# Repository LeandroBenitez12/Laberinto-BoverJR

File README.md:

# Robot en Desarrollo para la Resolución de Laberintos 🚧

## Descripción del Proyecto

Este repositorio contiene el código y los recursos utilizados para el desarrollo de un robot resolvente de laberintos, creado por Leandro Benitez, Ezequiel Sierra iniciado en 2022 acompañado de nuestro Profesor Ing. Bustos Mariano en el "Industrial de Temperley" ,como parte de un emocionante proyecto para la resolución autónoma de laberintos y la participacion competitiva a nivel nacional en la LNR Argentina. Durante el proceso de creación, hemos estado trabajando arduamente para implementar algoritmos de búsqueda, controladores PID, y trabajar con sensores Sharp y la programación en un microcontrolador ESP32 con el entorno Arduino. También hemos diseñado y creado nuestras propias librerías específicas para el robot, además de experimentar con la utilización de máquinas de estados y Programación orientada a Objetos para lograr un funcionamiento eficiente y preciso.
Actualmente nos encontramos Sponsoreados por PCBWAY.COM donde diseñamos la nueva Version de Bover JR y esperamos competir durante 2023 y 2024 en la LNR , quiero agradecer a **PCBWAY** por financiar el PCB!!!

## Características del Proyecto en Desarrollo

- **Resolución autónoma de laberintos:** Estamos trabajando para permitir que el robot navegue y encuentre la salida de un laberinto sin intervención externa y en el menor tiempo posible.
- **Algoritmos de búsqueda:** Hemos comenzado a implementar diferentes algoritmos de búsqueda para dotar al robot de la capacidad de tomar decisiones inteligentes mientras explora el laberinto.
- **Controladores PID:** Utilizamos controladores PID para mejorar la precisión y estabilidad del robot al seguir una trayectoria y evitar desviaciones indeseadas.
- **Sensores Sharp:** Integración de sensores Sharp para detectar obstáculos y evitar colisiones durante el recorrido del laberinto.
- **ESP32 y Arduino:** El robot se basa en un ESP32 programado con el entorno Arduino, lo que nos brindó flexibilidad y recursos para desarrollar un sistema eficiente y la utilización de Bluetooth para debugear.
- **Librerías personalizadas:** Creamos librerías específicas para nuestro robot, lo que facilitó el manejo y organización del código.

## Estructura del Repositorio

- **/Software:** Aquí se encuentran los códigos que estuvimos trabajando en el laberinto con sus librerías.
- **/Design 3D:** Aqui se encuentran los 3D diseñados para el robot Bover JR 

## Cómo Contribuir

¡Valoramos cualquier contribución que puedas brindar para mejorar nuestro proyecto! Si deseas colaborar, sugerir mejoras o corregir problemas, sigue estos pasos:

1. Haz un fork de este repositorio y clona tu copia localmente.
2. Realiza los cambios y mejoras en tu rama, incluso si es para sugerir posibles soluciones o nuevas ideas.
3. Asegúrate de agregar o actualizar la documentación con tus contribuciones.
4. Realiza un pull request a nuestra rama principal para que podamos revisar y considerar tus aportes.

## Contacto

Nos encantaría recibir tus comentarios, sugerencias y cualquier tipo de feedback que nos ayude a mejorar nuestro proyecto. Si deseas ponerte en contacto con nosotros, no dudes en escribirnos a:

- Leandro Benitez: leandrobenitezz2004@gmail.com
- Empresa : bovergroup@gmail.com

## Sigue actualizado al proyecto siguiendonos en: 
<p align="left">

</p>

## Agradecimientos

Queremos expresar nuestro agradecimiento a todas las personas que nos han brindado apoyo y colaboración en este proyecto, especialmente a **PCBWAY.COM** por sponsorear este proyecto. ¡Sin su ayuda, no habríamos llegado tan lejos en nuestro desarrollo!

## Videos

https://github.com/LeandroBenitez12/Laberinto-BoverJR/assets/108737751/4792c012-6e11-466b-b290-4252d44b76c1

https://github.com/LeandroBenitez12/Laberinto-BoverJR/assets/108737751/9e88a07d-3f39-4b07-be96-34b641f0b9c9

https://github.com/LeandroBenitez12/Laberinto-BoverJR/assets/108737751/d4477cc3-5138-43af-baba-faa490c5ad7a

Estamos entusiasmados con los avances que hemos logrado hasta el momento, pero reconocemos que aún hay mucho trabajo por delante. Apreciamos tu comprensión y paciencia mientras continuamos mejorando y refinando nuestro robot resolvente de laberintos. Puedes seguir actualizado al proyecto siguiendonos en nuestras redes sociales:
🤖🏆

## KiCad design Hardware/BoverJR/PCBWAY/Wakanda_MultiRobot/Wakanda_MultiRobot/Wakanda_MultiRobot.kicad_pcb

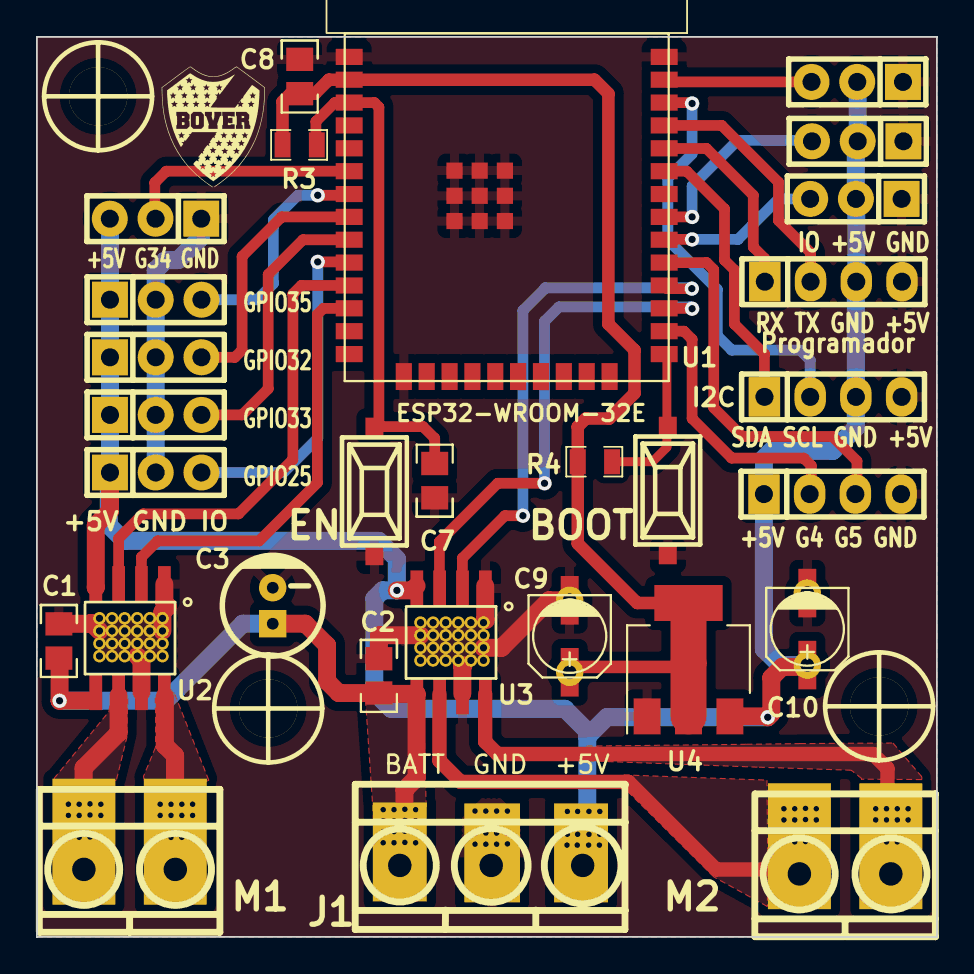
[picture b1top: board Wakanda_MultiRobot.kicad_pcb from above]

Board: 2 copper layers, 50.0 x 50.0 mm, 33 parts (0 on the bottom side), 28 nets.

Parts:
BOOT1: BOOT; Pulsador_SMD_2_BAJO
C1, C2, C7, C8: 100nF; C_0805
C3: 100uF 35V; CAP_ELEC_5x11mm
C9: 100uF; CAP_ELEC_SMD_4X5.5
C10: 10uF; CAP_ELEC_SMD_4X5.5
EN1: EN; Pulsador_SMD_2_BAJO
J1: Alimentacion; BORNERA3_AZUL_VIAS
J2, J4, J5, J6: Conn_01X03; Pin_Strip_3
J3: Sensor Distancia 1; Pin_Strip_3
J7: TATAMI Frontal Izquierdo; Pin_Strip_3
J8: Pin_Strip_3
J9: Programador; pin_strip_4
J10: I2C; pin_strip_4
J11: M1; BORNERA2_AZUL_VIAS
J12: M2; BORNERA2_AZUL_VIAS
J14: RANDOM; pin_strip_4
LOGO1: Mounting_Hole; Bover_Huella_frontal_FCU
P2, P3, P4: Mounting_Hole; Separador_M3_5mm
R3, R4: 10K; R_0805
SW1: START; Pin_Strip_3
U1: ESP32-WROOM-32E
U2, U3: TB67H451AFNG; SSOP-8_disipa
U4: AMS1117-3.3; SOT-223-3_TabPin2

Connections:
+3V3: C8.1, C9.1, R3.2, R4.2, U1.3V3, U4.2 (VO)
+5V: C10.1, J1.3, J2.1, J3.1, J4.1, J5.2, J6.2, J7.2, J8.1, J9.3, J10.3, J14.1, SW1.3, U2.4 (VREF), U3.4 (VREF), U4.3 (VI)
/EN: C7.1, EN1.2, R3.1, U1.9 (EN)
/GPIO4: J14.2, U1.24 (IO4)
/GPIO5: J14.3, U1.34 (IO5)
/IO0: BOOT1.2, R4.1, U1.23 (IO0)
/M_DER_A: U1.27 (IO17), U3.2 (IN2)
/M_DER_B: U1.25 (IO16), U3.3 (IN1)
/M_IZQ_A: U1.16 (IO27), U2.2 (IN2)
/M_IZQ_B: U1.15 (IO26), U2.3 (IN1)
/RXD: J9.1, U1.40 (RXD0)
/SCL: J10.2, U1.39 (IO22)
/SDA: J10.1, U1.42 (IO21)
/SENSOR1: J3.3, U1.13 (IO33)
/SENSOR2: J2.3, U1.14 (IO25)
/SENSOR3: J5.3, U1.38 (IO19)
/SENSOR4: J6.3, U1.35 (IO18)
/SENSOR5: J4.3, U1.11 (IO35)
/SENSOR6: J7.3, U1.36 (IO23)
/SENSOR7: J8.3, U1.12 (IO32)
/START: SW1.2, U1.10 (IO34)
/TXD: J9.2, U1.41 (TXD0)
GND: BOOT1.1, C1.2, C2.2, C3.2, C7.2, C8.2, C9.2, C10.2, EN1.1, J1.2, J2.2, J3.2, J4.2, J5.1, J6.1, J7.1, J8.2, J9.4, J10.4, J14.4, SW1.1, U1.GND, U2.1 (GND), U2.7 (RS), U3.1 (GND), U3.7 (RS), U4.1 (GND)
unnamed: J11.1, U2.6 (OUT1)
unnamed: J11.2, U2.8 (OUT2)
unnamed: J12.1, U3.6 (OUT1)
unnamed: J12.2, U3.8 (OUT2)
Vin: C1.1, C2.1, C3.1, J1.1, U2.5 (VM), U3.5 (VM)

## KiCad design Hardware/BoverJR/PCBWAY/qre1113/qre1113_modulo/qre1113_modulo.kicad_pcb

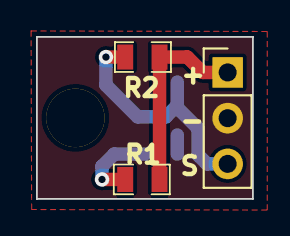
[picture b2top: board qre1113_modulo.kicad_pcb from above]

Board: 2 copper layers, 12.0 x 9.0 mm, 5 parts (1 on the bottom side), 4 nets.

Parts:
H1: HOLE; Separador_M3_5mm
J1: qre1113_out; PinHeader_1x03_P2.54mm_Vertical
R1: 100; R_0805
R2: 4k7; R_0805
U1: QRE1113GR; OnSemi_CASE100CY

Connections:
+3V3: J1.1, R1.1, R2.2
/OUT: J1.3, R2.1, U1.3
GND: J1.2, U1.2 (K), U1.4
unnamed: R1.2, U1.1 (A)

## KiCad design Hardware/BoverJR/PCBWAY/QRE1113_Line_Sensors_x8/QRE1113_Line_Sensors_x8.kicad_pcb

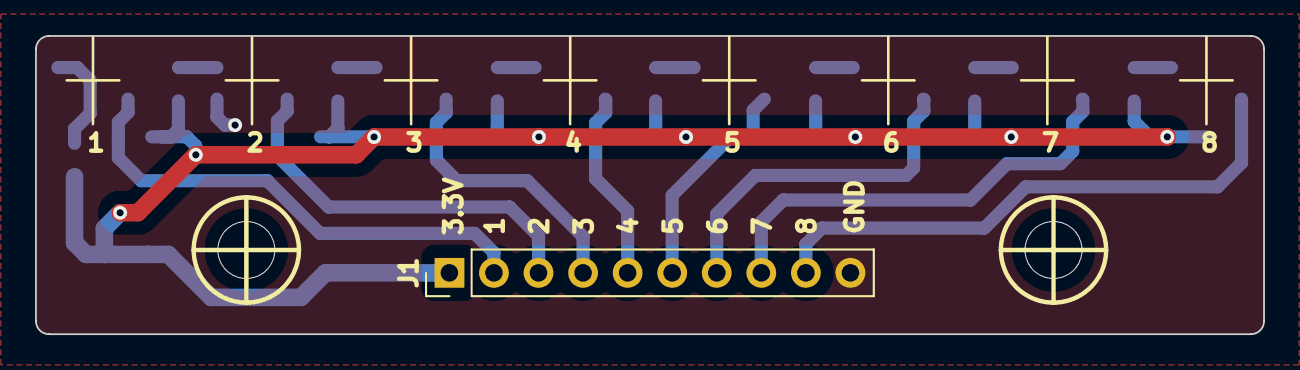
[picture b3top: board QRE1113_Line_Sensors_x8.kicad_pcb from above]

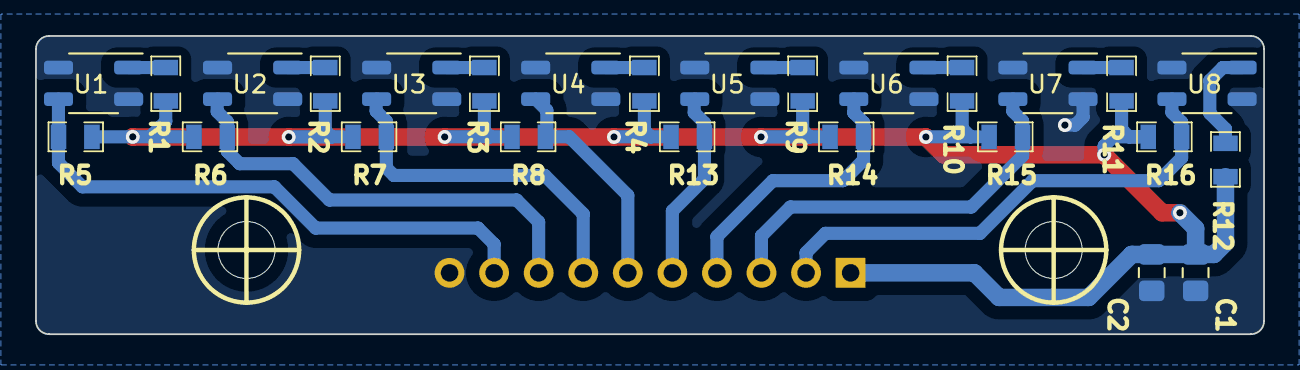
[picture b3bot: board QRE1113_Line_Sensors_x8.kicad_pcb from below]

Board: 2 copper layers, 70.0 x 17.0 mm, 29 parts (26 on the bottom side), 18 nets.

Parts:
C1, C2: 100nf; C_0805_2012Metric_Pad1.18x1.45mm_HandSolder
H1, H2: HOLE; Separador_M3_5mm
J1: Conn_01x10_Pin; PinHeader_1x10_P2.54mm_Vertical
R1, R2, R3, R4, R9, R10, R11, R12: 100; R_0805
R5, R6, R7, R8, R13, R14, R15, R16: 10k; R_0805
U1, U2, U3, U4, U5, U6, U7, U8: QRE1113GR; OnSemi_CASE100CY

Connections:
+3V3: C1.1, C2.1, J1.1, R1.1, R2.1, R3.1, R4.1, R5.2, R6.2, R7.2, R8.2, R9.1, R10.1, R11.1, R12.1, R13.2, R14.2, R15.2, R16.2
/OUT_1: J1.9, R5.1, U1.3
/OUT_2: J1.8, R6.1, U2.3
/OUT_3: J1.7, R7.1, U3.3
/OUT_4: J1.6, R8.1, U4.3
/OUT_5: J1.5, R13.1, U5.3
/OUT_6: J1.4, R14.1, U6.3
/OUT_7: J1.3, R15.1, U7.3
/OUT_8: J1.2, R16.1, U8.3
GND: C1.2, C2.2, J1.10, U1.2 (K), U1.4, U2.2 (K), U2.4, U3.2 (K), U3.4, U4.2 (K), U4.4, U5.2 (K), U5.4, U6.2 (K), U6.4, U7.2 (K), U7.4, U8.2 (K), U8.4
unnamed: R1.2, U1.1 (A)
unnamed: R2.2, U2.1 (A)
unnamed: R3.2, U3.1 (A)
unnamed: R4.2, U4.1 (A)
unnamed: R9.2, U5.1 (A)
unnamed: R10.2, U6.1 (A)
unnamed: R11.2, U7.1 (A)
unnamed: R12.2, U8.1 (A)

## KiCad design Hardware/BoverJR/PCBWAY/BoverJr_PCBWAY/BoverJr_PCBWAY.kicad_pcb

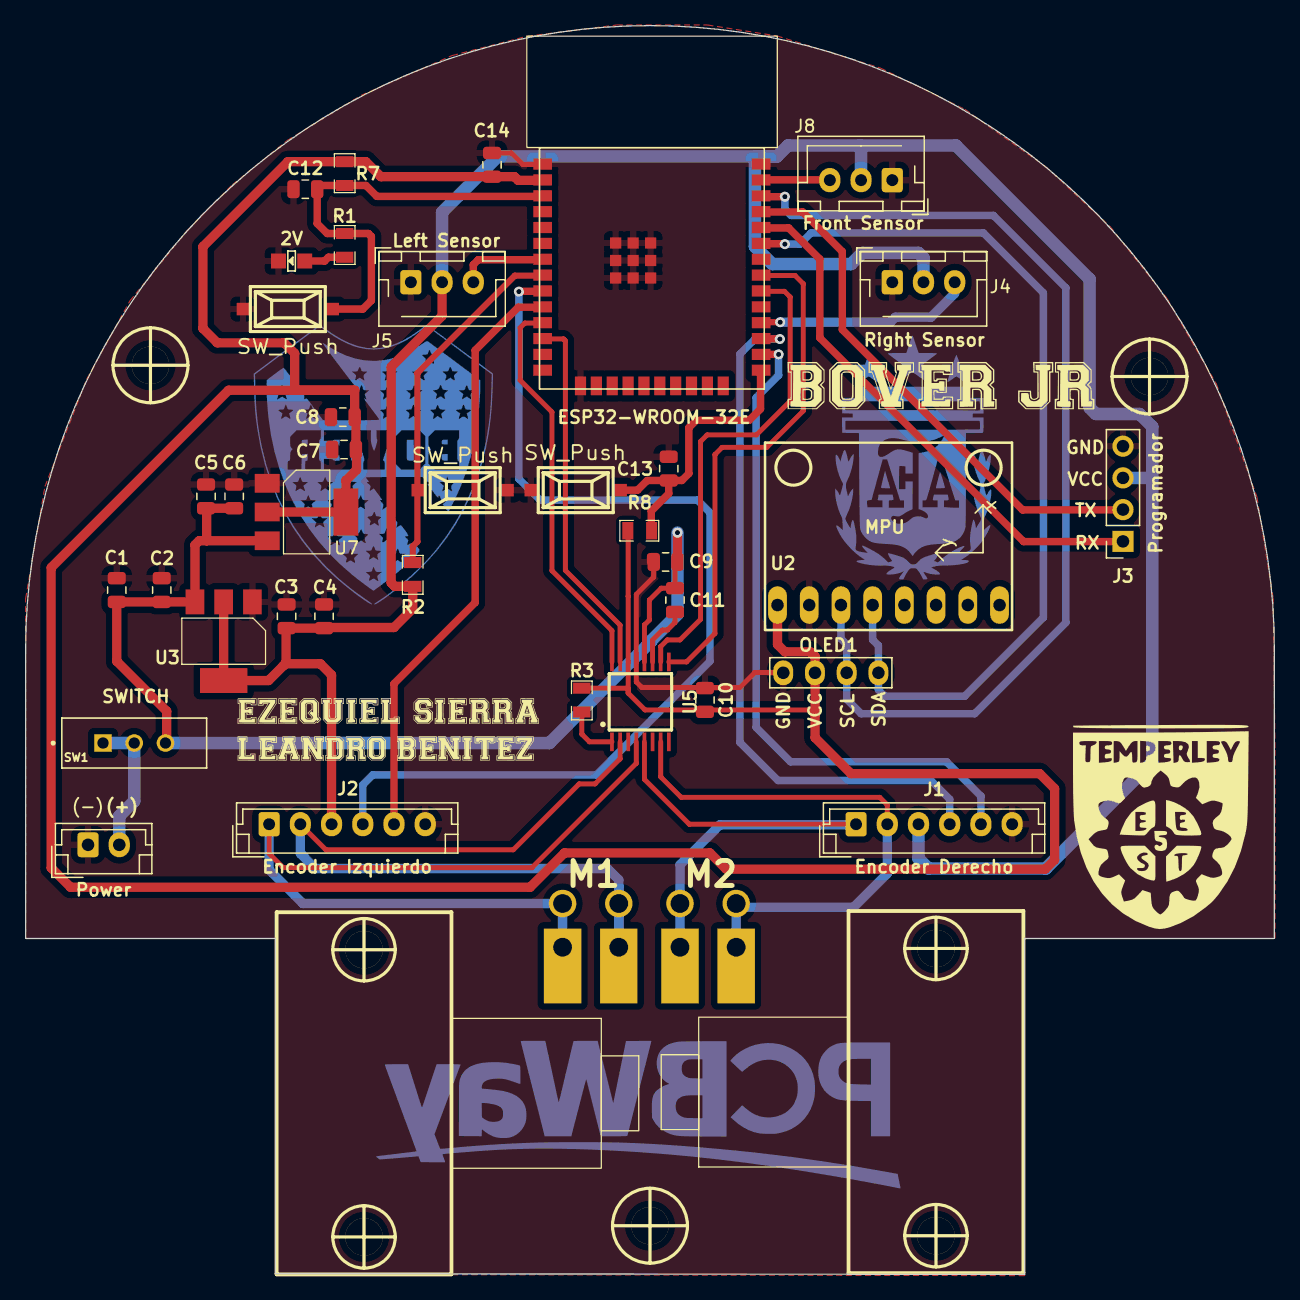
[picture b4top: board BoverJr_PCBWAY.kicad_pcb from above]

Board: 2 copper layers, 100.0 x 100.0 mm, 53 parts (1 on the bottom side), 30 nets.

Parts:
C1, C4, C5, C8, C9: 10uF; C_0805_2012Metric
C2, C3, C6, C7, C14: 100nF; C_0805_2012Metric
C10: 2,2uF; C_0805_2012Metric
C11: 10nF; C_0805_2012Metric
C12, C13: 1nf; C_0805_2012Metric
G1: LOGO_EESTN5_2; EESTN5
G2: LOGO; Bover_Huella_BCU_SOLK
G3: LOGO; AFA_BCU_filks
G6: LOGO; BOVER_NAME
G10: LOGO; Leandro
G11: LOGO; ezequiel
G14: LOGO; logo_pcbway
H1: Soporte_Motor_IZQ; Pololu_Micro_Con_Soporte_Simple
H2: Soporte_Motor_DER; Pololu_Micro_Con_Soporte_Simple
H3, H4, H5: Mounting_Hole; hole_3mm
J1: Encoder Derecho; JST_EH_B6B-EH-A_1x06_P2.50mm_Vertical
J2: Encoder Izquierdo; JST_EH_B6B-EH-A_1x06_P2.50mm_Vertical
J3: Programador; PinSocket_1x04_P2.54mm_Vertical
J4: Distancia_Der; JST_XH_B3B-XH-AM_1x03_P2.50mm_Vertical
J5: Distancia_Izq; JST_XH_B3B-XH-AM_1x03_P2.50mm_Vertical
J6, J7, J9, J11: Cable_PAD; Cable_Doble_1,5mm
J8: Distancia_Frontal; JST_XH_B3B-XH-AM_1x03_P2.50mm_Vertical
J10: 7.4v; JST_EH_B2B-EH-A_1x02_P2.50mm_Vertical
LED_ESP32: 2V; Led_0805
OLED1: SSD1306-SSD1306-128x64_OLED; 128x64OLED
R1: 470; R_0805
R2, R7: 10K; R_0805
R3: 47K; R_0805
R8: 1OK; R_0805
SW1: SW_SPDT; SW_MINI-SPDT-SW
SW_BOOT1: SW_Push; Pulsador_SMD_2_BAJO
SW_EN1: SW_Push; Pulsador_SMD_2_BAJO
SW_START1: SW_Push; Pulsador_SMD_2_BAJO
U1: ESP32-WROOM-32E
U2: MPU; MPU-6050
U3: AMS1117-5.0; SOT-223-3_TabPin2
U5: DRV8833; HTSSOP-16
U7: AMS1117-3.3; SOT-223-3_TabPin2

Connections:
+3.3V: C7.1, C8.1, C10.2, C14.1, OLED1.2 (VCC), R3.1, R7.2, R8.2, U1.3V3, U2.1 (VCC), U5.14 (VINT), U7.2 (VO)
+5V: C3.2, C4.1, J1.3, J2.3, J3.3, J4.2, J5.2, J8.2, R2.2, U3.2 (VO)
+BATT: J10.2, SW1.1 (A), SW1.2 (B)
/BOOT: C13.2, R8.1, SW_BOOT1.2, U1.23 (IO0)
/EN: C12.2, R1.2, R7.1, SW_EN1.2, U1.9 (EN)
/IR_DER: J5.3, U1.11 (IO35)
/IR_FRONTAL: J8.3, U1.36 (IO23)
/IR_IZQ: J4.3, U1.27 (IO17)
/M1_IN1: U1.38 (IO19), U5.9 (BIN1)
/M1_IN2: U1.35 (IO18), U5.10 (BIN2)
/M2_IN1: U1.15 (IO26), U5.16 (AIN1)
/M2_IN2: U1.16 (IO27), U5.15 (AIN2)
/OUT_A_MOTOR1: J1.1, J6.1, U5.5 (BOUT2)
/OUT_A_MOTOR2: J2.1, J9.1, U5.4 (AOUT2)
/OUT_B_MOTOR1: J1.2, J7.1, U5.7 (BOUT1)
/OUT_B_MOTOR2: J2.2, J11.1, U5.2 (AOUT1)
/OUT_M1_DA: J1.4, U1.25 (IO16)
/OUT_M1_DB: J1.5, U1.24 (IO4)
/OUT_M2_DA: J2.4, U1.13 (IO33)
/OUT_M2_DB: J2.5, U1.14 (IO25)
/RX: J3.1, U1.40 (RXD0)
/SCL: OLED1.3 (SCL), U1.39 (IO22), U2.3 (SCL)
/SDA: OLED1.4 (SDA), U1.42 (IO21), U2.4 (SDA)
/START: R2.1, SW_START1.2, U1.12 (IO32)
/TX: J3.2, U1.41 (TXD0)
GND: C1.2, C2.2, C3.1, C4.2, C5.2, C6.2, C7.2, C8.2, C9.1, C10.1, C12.1, C13.1, C14.2, J1.6, J2.6, J3.4, J4.1, J5.1, J8.1, J10.1, LED_ESP32.2 (K), OLED1.1 (GND), SW_BOOT1.1, SW_EN1.1, SW_START1.1, U1.GND, U2.2 (GND), U3.1 (GND), U5.13 (GND), U7.1 (GND)
unnamed: LED_ESP32.1 (A), R1.1
unnamed: C11.2, U5.11 (VCP)
unnamed: R3.2, U5.1 (nSLEEP)
VCC: C1.1, C2.1, C5.1, C6.1, C9.2, C11.1, SW1.3 (C), U3.3 (VI), U5.12 (VM), U7.3 (VI)

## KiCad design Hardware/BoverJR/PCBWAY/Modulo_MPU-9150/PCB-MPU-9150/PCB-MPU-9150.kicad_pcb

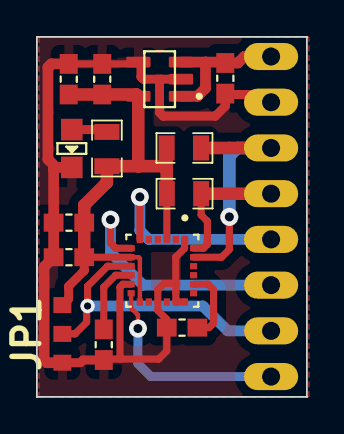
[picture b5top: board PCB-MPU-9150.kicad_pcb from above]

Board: 2 copper layers, 15.0 x 20.0 mm, 15 parts (1 on the bottom side), 12 nets.

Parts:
C1: 2.2nF; C_0603
C2, C3, C5: 100nF; C_0603
C4: 10nF; C_0603
C6: 10uF; C_0603
C7: 4.7uF; C_0603
JP1: Jump; R_0805
LED1: LED; Led_0805
P1: CONN_01X08; GY-521-MPU-6050
R1, R2: 10K; R_0805
R3: 1K; R_0805
U1: MPU-9150; MPU-9150-Qfn-24
U2: AP2112K-3.3; AP2112K-3.3-Sot25

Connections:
+3.3V: C3.1, C4.1, C5.2, C6.2, JP1.3 (B), R1.1, R2.1, R3.1, U1.3 (VDD), U1.8 (VLOGIC), U1.13 (VDD), U2.5 (VOUT)
/AD0: JP1.2 (C), P1.7, U1.9 (AD0)
/INT: P1.8, U1.12 (INT)
/SCL: P1.3, R2.2, U1.23 (SCL)
/SDA: P1.4, R1.2, U1.24 (SDA)
/XCL: P1.6, U1.7 (ES_CL)
/XDA: P1.5, U1.6 (ES_DA)
GND: C1.1, C2.1, C3.2, C4.2, C5.1, C6.1, C7.2, JP1.1 (A), LED1.2 (K), P1.2, U1.1 (CLKIN), U1.11 (FSYNC), U1.15 (GND), U1.17 (GND), U1.18 (GND), U2.2 (GND)
unnamed: LED1.1 (A), R3.2
unnamed: C1.2, U1.20 (CPOUT)
unnamed: C2.2, U1.10 (REGOUT)
VCC: C7.1, P1.1, U2.1 (VIN), U2.3 (EN)

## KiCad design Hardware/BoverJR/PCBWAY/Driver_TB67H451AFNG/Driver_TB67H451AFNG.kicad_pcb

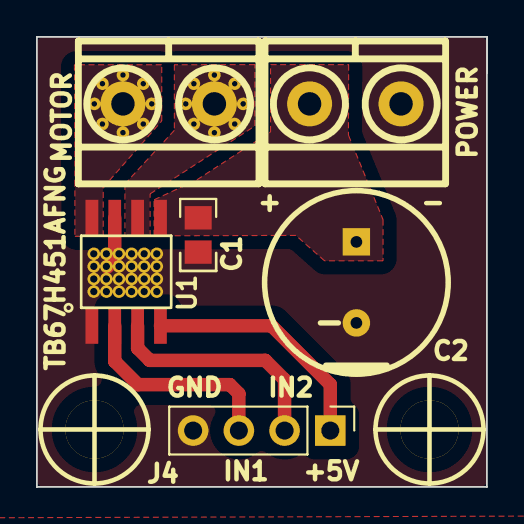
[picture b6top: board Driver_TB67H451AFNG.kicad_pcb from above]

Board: 2 copper layers, 25.0 x 25.0 mm, 8 parts (0 on the bottom side), 7 nets.

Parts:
C1: 100nF; C_0805
C2: 100uF 35V; CAP_ELEC_10X8mm
H1, H2: Mounting_Hole; Separador_M3_5mm
J1: POWER; BORNERA2_AZUL
J3: MOTOR; BORNERA2_AZUL_HOLES+
J4: Conn_01x04_Pin; PinHeader_1x04_P2.54mm_Vertical
U1: TB67H451AFNG; SSOP-8_disipa

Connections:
+5V: J4.1, U1.4 (VREF)
/M1A: J4.3, U1.2 (IN2)
/M1B: J4.2, U1.3 (IN1)
/Vin: C1.1, C2.1, J1.2, U1.5 (VM)
GND: C1.2, C2.2, J1.1, J4.4, U1.1 (GND), U1.7 (RS)
unnamed: J3.1, U1.6 (OUT1)
unnamed: J3.2, U1.8 (OUT2)

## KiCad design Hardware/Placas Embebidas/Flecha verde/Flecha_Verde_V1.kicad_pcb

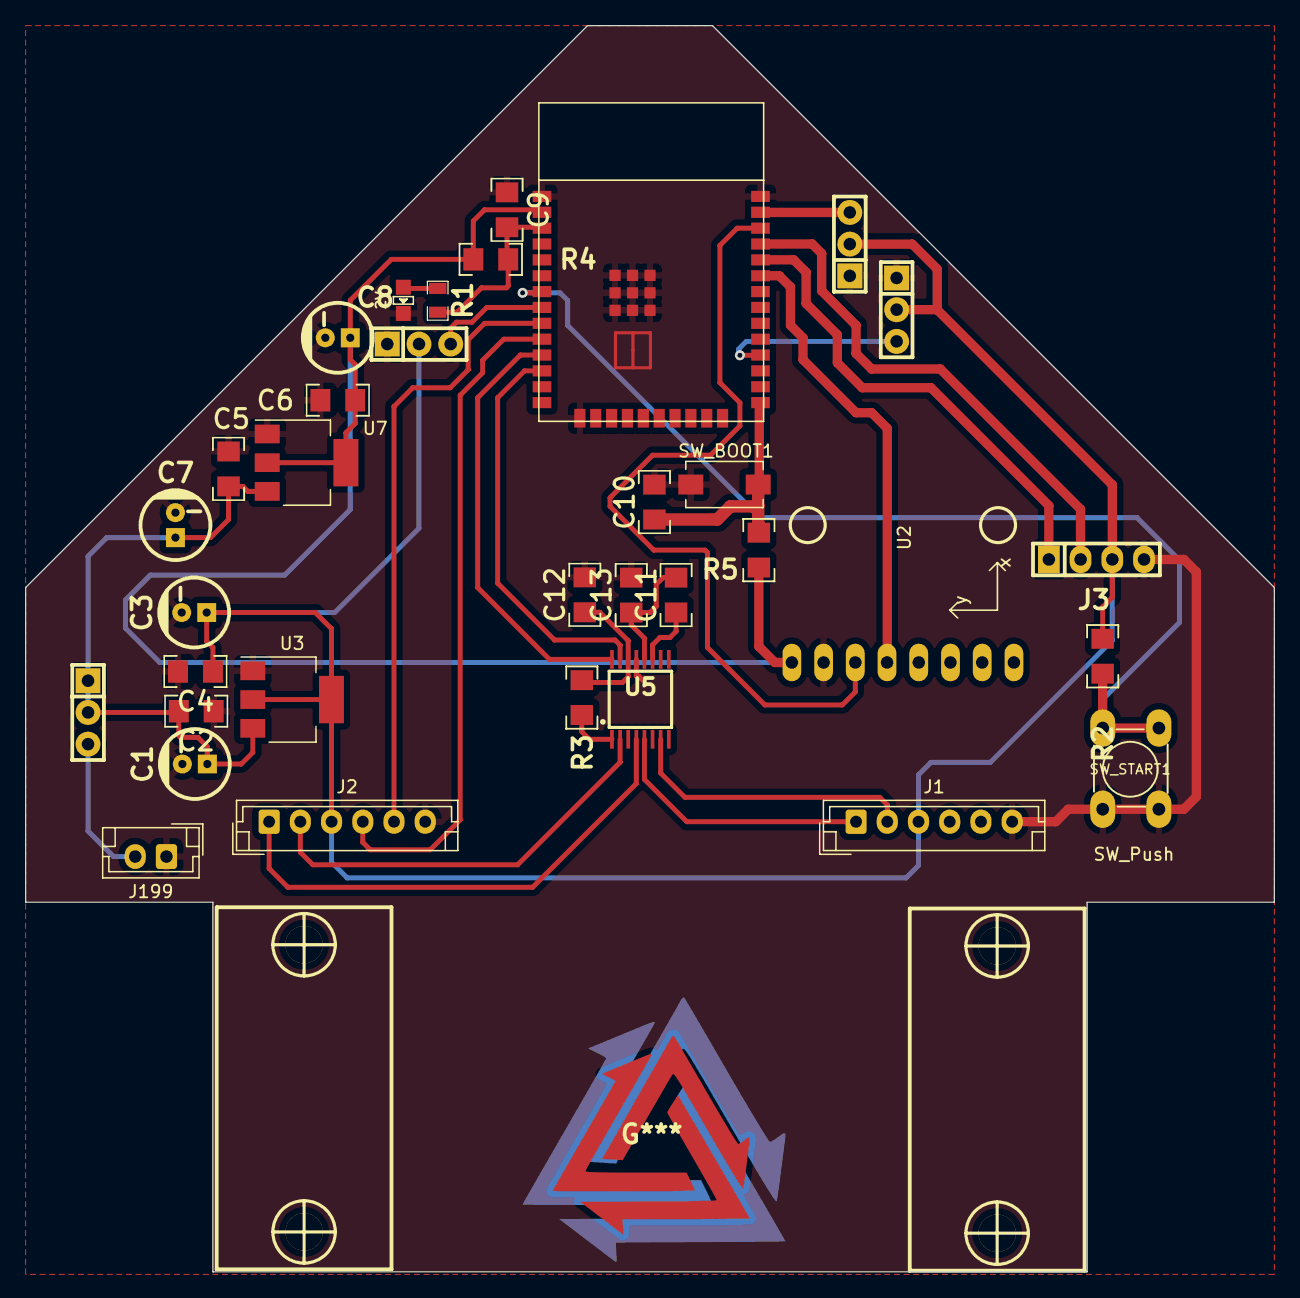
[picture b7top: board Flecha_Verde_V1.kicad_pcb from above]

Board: 2 copper layers, 100.0 x 99.8 mm, 36 parts (0 on the bottom side), 30 nets.

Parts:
C1, C3, C7, C8: 10uF; CAP_ELEC_5x11mm
C2, C4, C5, C6, C9, C10: 100nF; C_1206
C11: 10nF; C_1206
C12: 2,2uF; C_1206
C13: 10uF; C_1206
H1: MOTOR_IZQ; Pololu_Micro_Con_Soporte_Simple
H2: MOTOR_DER; Pololu_Micro_Con_Soporte_Simple
J1: Encoder Derecho; JST_EH_B6B-EH-A_1x06_P2.50mm_Vertical
J2: Encoder Izquierdo; JST_EH_B6B-EH-A_1x06_P2.50mm_Vertical
J3: Programador; pin_strip_4
J4: Distancia_Der; Pin_Strip_3
J5: Distancia_Izq; Pin_Strip_3
J8: Distancia_Frontal; Pin_Strip_3
J199: 7.4v; JST_EH_B2B-EH-A_1x02_P2.50mm_Vertical
J299: Jumper; Pin_Strip_3
LED_ESP32: 2V; Led_0805
R1: 470; R_0805
R2, R5: 10K; R_1206
R3: 47K; R_1206
R4: 10k; R_1206
SW_BOOT1: SW_Push; SW_SPST_EVQPE1
SW_START1: SW_Push; PUSH_SWITCH_THT
U1: ESP32-WROOM-32E
U2: MPU; MPU-6050
U3: AMS1117-5.0; SOT-223-3_TabPin2
U5: DRV8833; HTSSOP-16
U7: AMS1117-3.3; SOT-223-3_TabPin2

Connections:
+3.3V: C6.1, C8.1, C12.2, R3.1, R4.1, R5.1, U1.2 (VDD), U2.1 (VCC), U5.14 (VINT), U7.2 (VO)
+5V: C3.1, C4.2, J1.3, J2.3, J3.3, J4.2, J5.2, J8.2, R2.1, U3.2 (VO)
+BATT: C1.1, C2.1, C5.1, C7.1, C11.1, C13.2, J299.1, J299.2, U3.3 (VI), U5.12 (VM), U7.3 (VI)
/BOOT: C10.2, R5.2, SW_BOOT1.2, U1.25 (IO0)
/EN: C9.1, R1.2, R4.2, U1.3 (EN)
/IR_DER: J5.3, U1.8 (IO32)
/IR_FRONTAL: J8.3, U1.37 (IO23)
/IR_IZQ: J4.3, U1.28 (IO17)
/M1_IN1: U1.31 (IO19), U5.9 (BIN1)
/M1_IN2: U1.30 (IO18), U5.10 (BIN2)
/M2_IN1: U1.11 (IO26), U5.16 (AIN1)
/M2_IN2: U1.12 (IO27), U5.15 (AIN2)
/OUT_A_MOTOR1: J1.1, U5.5 (BOUT2)
/OUT_A_MOTOR2: J2.1, U5.4 (AOUT2)
/OUT_B_MOTOR1: J1.2, U5.7 (BOUT1)
/OUT_B_MOTOR2: J2.2, U5.2 (AOUT1)
/OUT_M1_DA: J1.4, U1.27 (IO16)
/OUT_M1_DB: J1.5, U1.26 (IO4)
/OUT_M2_DA: J2.4, U1.10 (IO25)
/OUT_M2_DB: J2.5, U1.9 (IO33)
/RX: J3.1, U1.34 (IO3)
/SCL_MPU6050: U1.36 (IO22), U2.3 (SCL)
/SDA_MPU6050: U1.33 (IO21), U2.4 (SDA)
/START: R2.2, SW_START1.2, U1.7 (IO35)
/TX: J3.2, U1.35 (IO1)
GND: C1.2, C2.2, C3.2, C4.1, C5.2, C6.2, C7.2, C8.2, C9.2, C10.1, C12.1, C13.1, J1.6, J2.6, J3.4, J4.1, J5.1, J8.1, J199.1, LED_ESP32.2 (K), SW_BOOT1.1, SW_START1.1, U1.1 (GND@1), U1.15 (GND@15), U1.38 (GND@38), U1.GND@39 (THERMAL@39), U1.GND@40 (THERMAL@39), U1.GND@41 (THERMAL@39), U1.GND@42 (THERMAL@39), U1.GND@43 (THERMAL@39), U1.GND@44 (THERMAL@39), U1.GND@45 (THERMAL@39), U1.GND@46 (THERMAL@39), U1.GND@47 (THERMAL@39), U2.2 (GND), U3.1 (GND), U5.13 (GND), U7.1 (GND)
unnamed: J199.2, J299.3
unnamed: LED_ESP32.1 (A), R1.1
unnamed: C11.2, U5.11 (VCP)
unnamed: R3.2, U5.1 (nSLEEP)

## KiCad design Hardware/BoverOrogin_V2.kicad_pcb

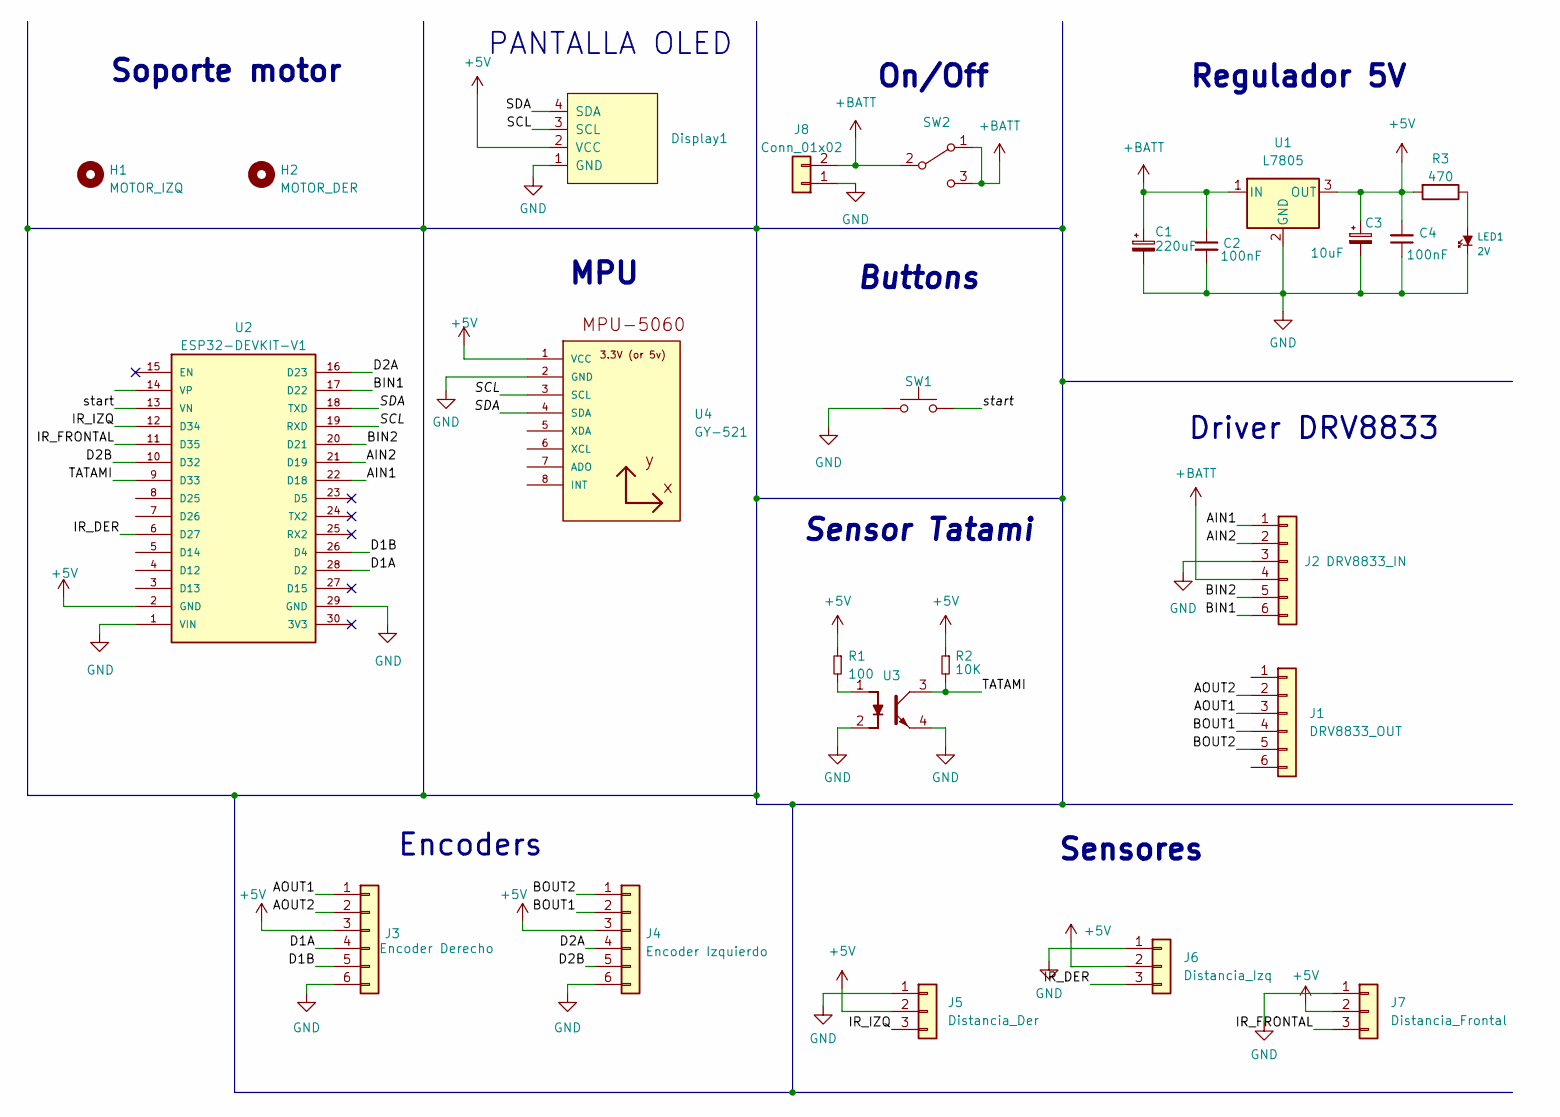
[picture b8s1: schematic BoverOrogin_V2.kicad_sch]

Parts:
C1: 220uF; C_1206
C2, C4: 100nF; C_1206
C3: 10uF; C_1206
Display1: SSD1306-SSD1306-128x64_OLED; 128x64OLED
H1: MOTOR_IZQ; Pololu_Micro_Con_Soporte_Simple
H2: MOTOR_DER; Pololu_Micro_Con_Soporte_Simple
J1: DRV8833_OUT; PinSocket_1x06_P2.54mm_Vertical
J2: DRV8833_IN; PinSocket_1x06_P2.54mm_Vertical
J3: Encoder Derecho; JST_EH_B6B-EH-A_1x06_P2.50mm_Vertical
J4: Encoder Izquierdo; JST_EH_B6B-EH-A_1x06_P2.50mm_Vertical
J5: Distancia_Der; JST_EH_B3B-EH-A_1x03_P2.50mm_Vertical
J6: Distancia_Izq; JST_EH_B3B-EH-A_1x03_P2.50mm_Vertical
J7: Distancia_Frontal; JST_EH_B3B-EH-A_1x03_P2.50mm_Vertical
J8: Conn_01x02; JST_EH_B2B-EH-A_1x02_P2.50mm_Vertical
LED1: 2V; led_3mm_clear
R1: 100; R_1206
R2: 10K; R_1206
R3: 470; R_0805
SW1: SW_Push; PUSH_SWITCH_THT
SW2: SW_SPDT; SW_SPDT_TH_Vertical
U1: L7805; SOT223
U2: ESP32-DEVKIT-V1; ESP32-DEVKIT-V1-30Pines
U3: QRE1113; QRE1113GR
U4: GY-521; MPU-6050

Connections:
+5V: C3.1, C4.2, J3.3, J4.3, J5.2, J6.2, J7.2, R1.1, R2.1, R3.2, U1.3 (OUT), U2.2 (GND), U4.1 (VCC)
+BATT: C1.1, C2.1, J2.4, J8.2, SW2.1 (A), SW2.2 (B), SW2.3 (C), U1.1 (IN)
/AIN1: J2.1, U2.22 (D18)
/AIN2: J2.2, U2.21 (D19)
/AOUT1: J1.3, J3.1
/AOUT2: J1.2, J3.2
/BIN1: J2.6, U2.17 (D22)
/BIN2: J2.5, U2.20 (D21)
/BOUT1: J1.4, J4.2
/BOUT2: J1.5, J4.1
/D1A: J3.4, U2.28 (D2)
/D1B: J3.5, U2.26 (D4)
/D2A: J4.4, U2.16 (D23)
/D2B: J4.5, U2.10 (D32)
/IR_DER: J6.3, U2.6 (D27)
/IR_FRONTAL: J7.3, U2.11 (D35)
/IR_IZQ: J5.3, U2.12 (D34)
/SCL: Display1.3 (SCL), U2.19 (RXD), U4.3 (SCL)
/SDA: Display1.4 (SDA), U2.18 (TXD), U4.4 (SDA)
/TATAMI: R2.2, U2.9 (D33), U3.3
/start: SW1.2, U2.13 (VN)
GND: C1.2, C2.2, C3.2, C4.1, J2.3, J3.6, J4.6, J5.1, J6.1, J7.1, J8.1, LED1.2 (K), SW1.1, U1.2 (GND), U2.1 (VIN), U2.29 (GND), U3.2, U3.4, U4.2 (GND)
unnamed: LED1.1 (A), R3.1
unnamed: R1.2, U3.1

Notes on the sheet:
Sensores
Soporte motor
Sensor Tatami
Buttons
Encoders
PANTALLA OLED
MPU
On/Off
Regulador 5V
Driver DRV8833

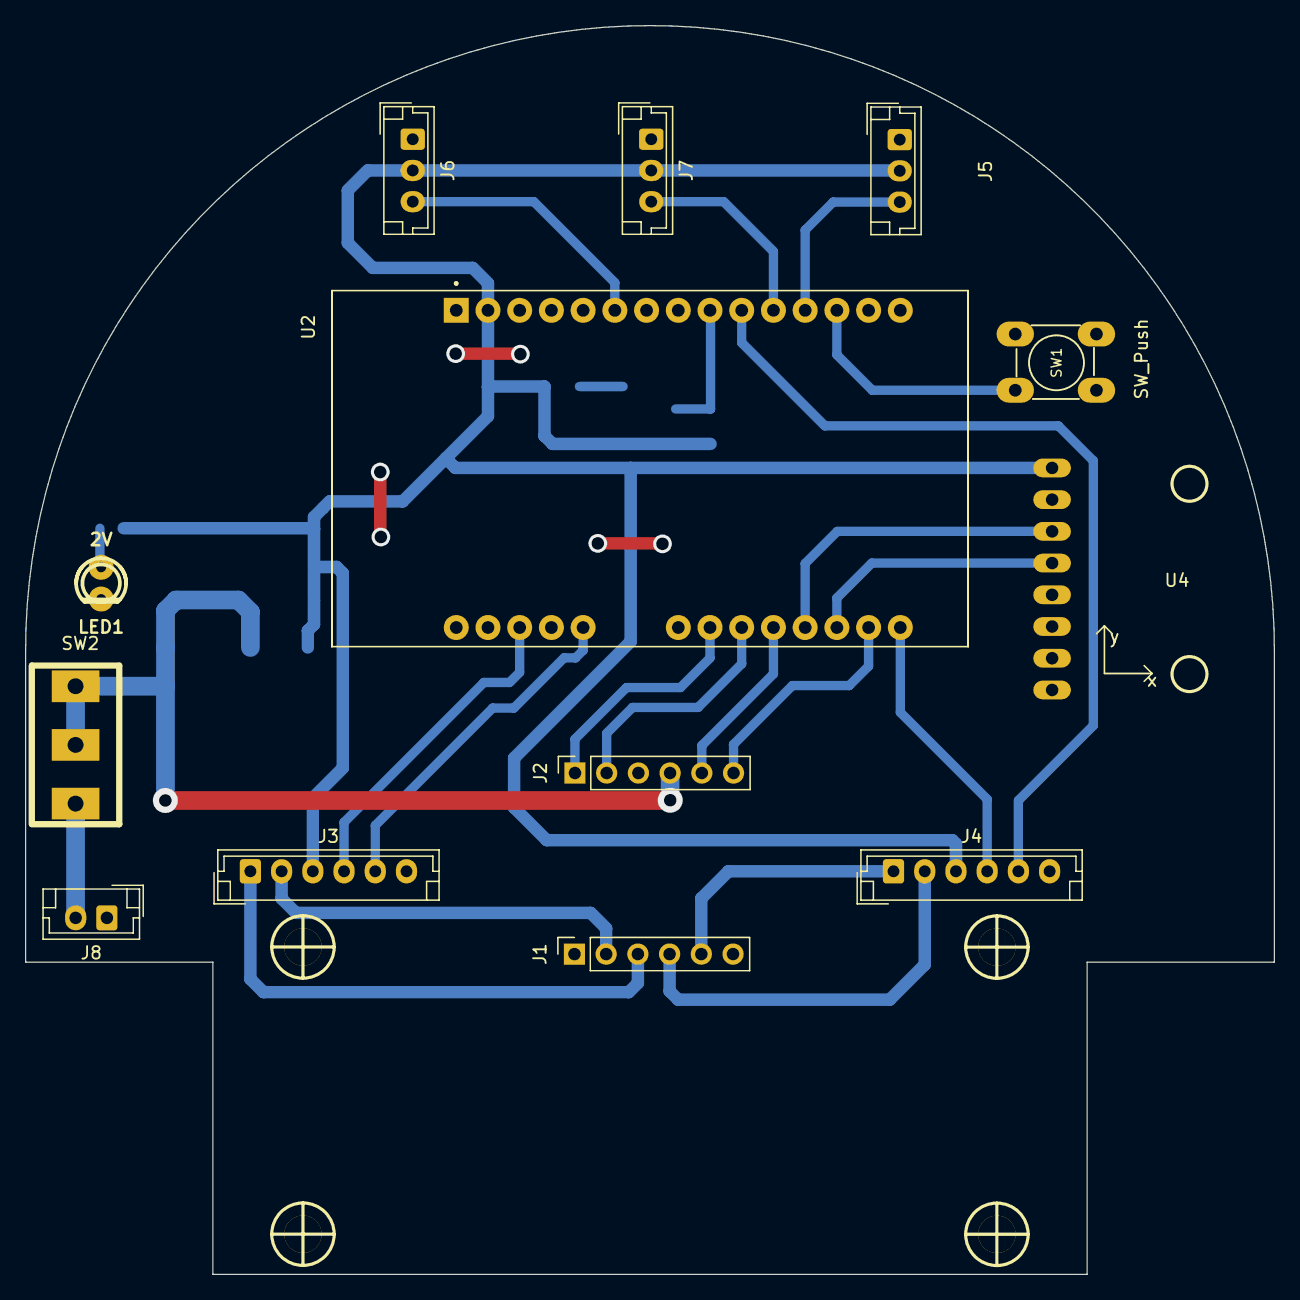
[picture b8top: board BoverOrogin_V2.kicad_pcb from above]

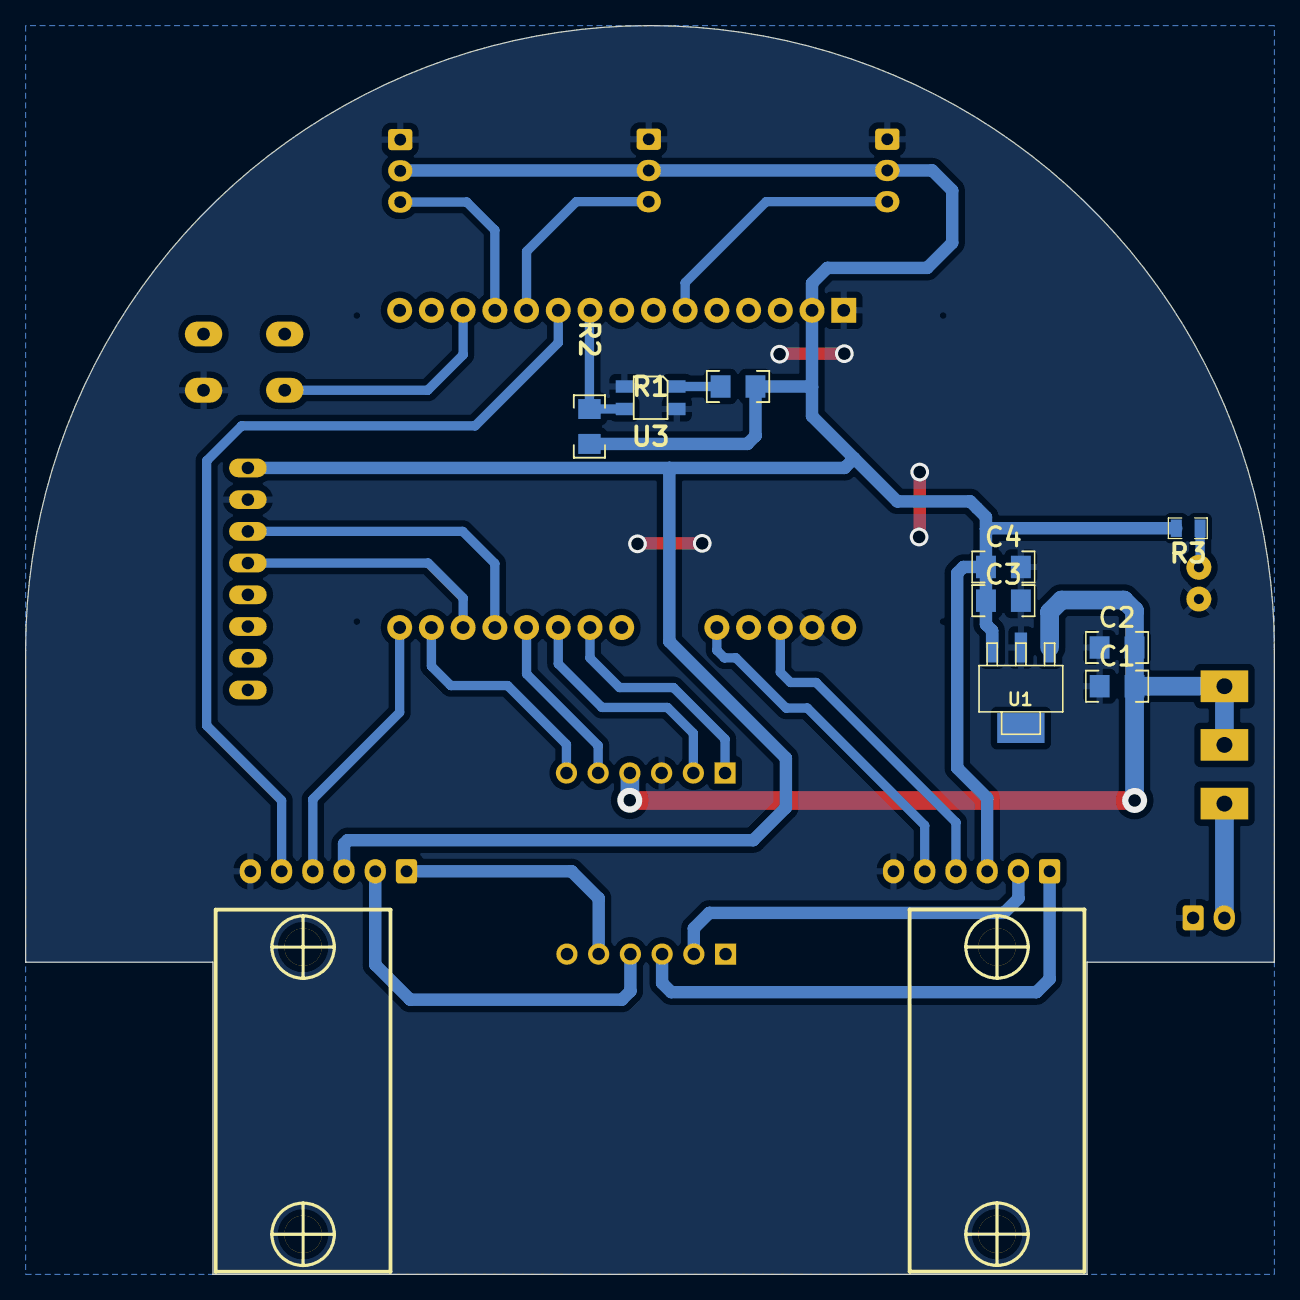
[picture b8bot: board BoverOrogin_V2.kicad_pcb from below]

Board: 2 copper layers, 100.0 x 100.0 mm, 24 parts (11 on the bottom side), 24 nets.
